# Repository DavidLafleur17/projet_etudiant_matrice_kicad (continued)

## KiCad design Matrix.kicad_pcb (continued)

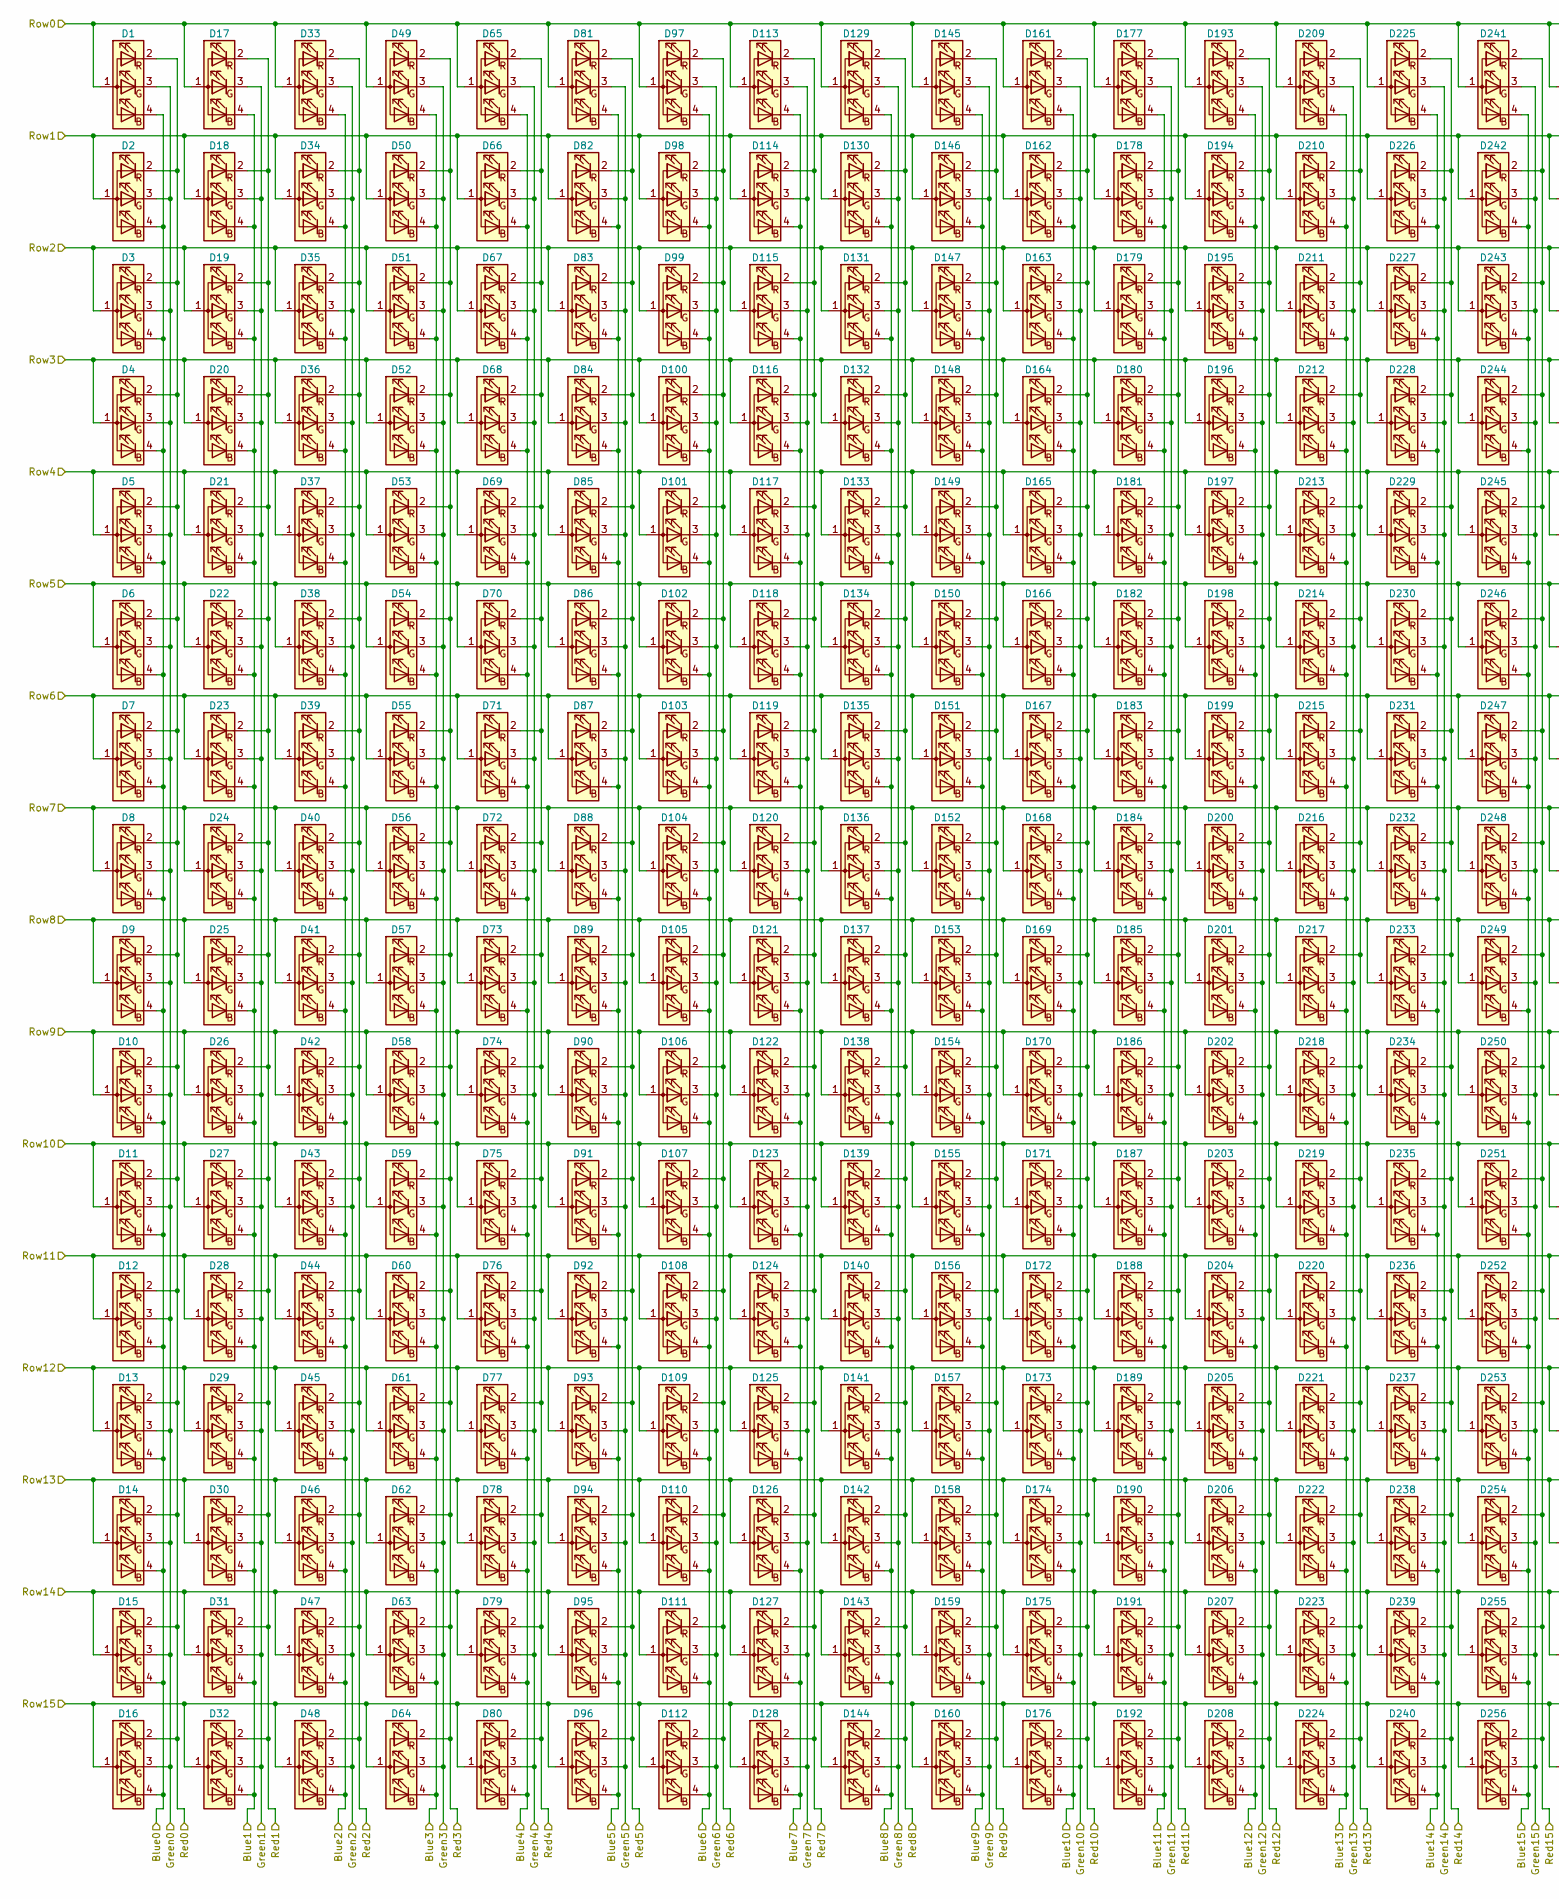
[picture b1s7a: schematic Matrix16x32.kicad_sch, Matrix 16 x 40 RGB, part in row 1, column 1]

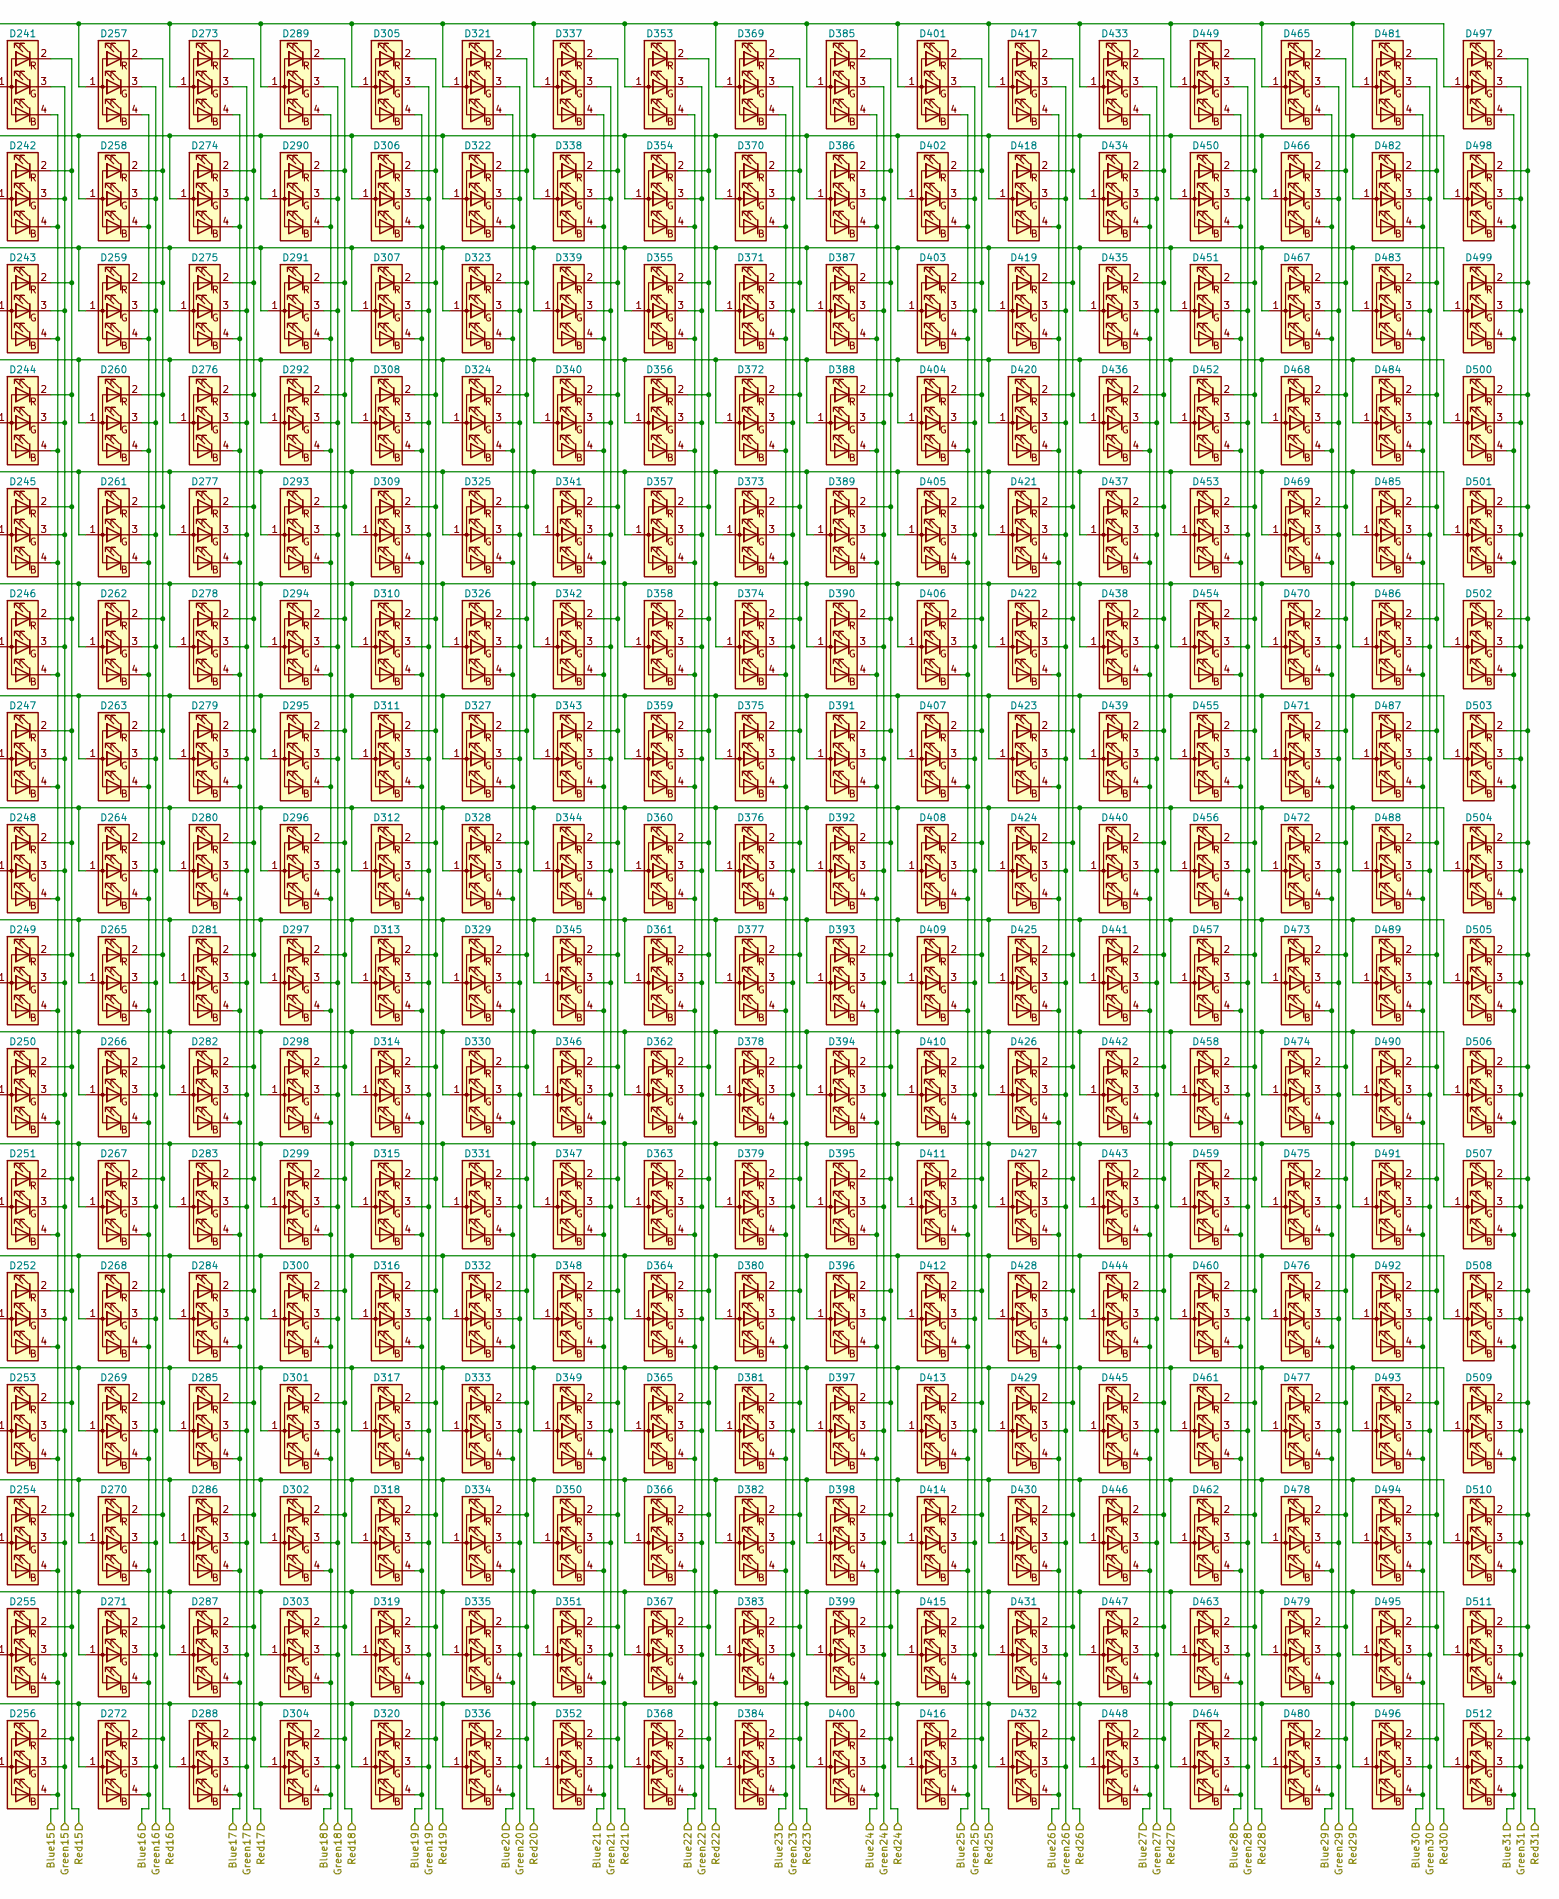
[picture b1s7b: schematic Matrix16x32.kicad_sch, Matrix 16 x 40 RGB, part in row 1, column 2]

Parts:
D1, D2, D3, D4, D5, D6, D7, D8, D9, D10, D11, D12, D13, D14, D15, D16, D17, D18, D19, D20, D21, D22, D23, D24, D25, D26, D27, D28, D29, D30, D31, D32, D33, D34, D35, D36, D37, D38, D39, D40, D41, D42, D43, D44, D45, D46, D47, D48, D49, D50, D51, D52, D53, D54, D55, D56, D57, D58, D59, D60, D61, D62, D63, D64, D65, D66, D67, D68, D69, D70, D71, D72, D73, D74, D75, D76, D77, D78, D79, D80, D81, D82, D83, D84, D85, D86, D87, D88, D89, D90, D91, D92, D93, D94, D95, D96, D97, D98, D99, D100, D101, D102, D103, D104, D105, D106, D107, D108, D109, D110, D111, D112, D113, D114, D115, D116, D117, D118, D119, D120, D121, D122, D123, D124, D125, D126, D127, D128, D129, D130, D131, D132, D133, D134, D135, D136, D137, D138, D139, D140, D141, D142, D143, D144, D145, D146, D147, D148, D149, D150, D151, D152, D153, D154, D155, D156, D157, D158, D159, D160, D161, D162, D163, D164, D165, D166, D167, D168, D169, D170, D171, D172, D173, D174, D175, D176, D177, D178, D179, D180, D181, D182, D183, D184, D185, D186, D187, D188, D189, D190, D191, D192, D193, D194, D195, D196, D197, D198, D199, D200, D201, D202, D203, D204, D205, D206, D207, D208, D209, D210, D211, D212, D213, D214, D215, D216, D217, D218, D219, D220, D221, D222, D223, D224, D225, D226, D227, D228, D229, D230, D231, D232, D233, D234, D235, D236, D237, D238, D239, D240, D241, D242, D243, D244, D245, D246, D247, D248, D249, D250, D251, D252, D253, D254, D255, D256, D257, D258, D259, D260, D261, D262, D263, D264, D265, D266, D267, D268, D269, D270, D271, D272, D273, D274, D275, D276, D277, D278, D279, D280, D281, D282, D283, D284, D285, D286, D287, D288, D289, D290, D291, D292, D293, D294, D295, D296, D297, D298, D299, D300, D301, D302, D303, D304, D305, D306, D307, D308, D309, D310, D311, D312, D313, D314, D315, D316, D317, D318, D319, D320, D321, D322, D323, D324, D325, D326, D327, D328, D329, D330, D331, D332, D333, D334, D335, D336, D337, D338, D339, D340, D341, D342, D343, D344, D345, D346, D347, D348, D349, D350, D351, D352, D353, D354, D355, D356, D357, D358, D359, D360, D361, D362, D363, D364, D365, D366, D367, D368, D369, D370, D371, D372, D373, D374, D375, D376, D377, D378, D379, D380, D381, D382, D383, D384, D385, D386, D387, D388, D389, D390, D391, D392, D393, D394, D395, D396, D397, D398, D399, D400, D401, D402, D403, D404, D405, D406, D407, D408, D409, D410, D411, D412, D413, D414, D415, D416, D417, D418, D419, D420, D421, D422, D423, D424, D425, D426, D427, D428, D429, D430, D431, D432, D433, D434, D435, D436, D437, D438, D439, D440, D441, D442, D443, D444, D445, D446, D447, D448, D449, D450, D451, D452, D453, D454, D455, D456, D457, D458, D459, D460, D461, D462, D463, D464, D465, D466, D467, D468, D469, D470, D471, D472, D473, D474, D475, D476, D477, D478, D479, D480, D481, D482, D483, D484, D485, D486, D487, D488, D489, D490, D491, D492, D493, D494, D495, D496, D497, D498, D499, D500, D501, D502, D503, D504, D505, D506, D507, D508, D509, D510, D511, D512: LED_ARGB; T2133BGR; DigiKey PN 3147-T2133BGR-20C0001U2U1930CT-ND

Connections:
/Blue0: D1.4 (BK), D2.4 (BK), D3.4 (BK), D4.4 (BK), D5.4 (BK), D6.4 (BK), D7.4 (BK), D8.4 (BK), D9.4 (BK), D10.4 (BK), D11.4 (BK), D12.4 (BK), D13.4 (BK), D14.4 (BK), D15.4 (BK), D16.4 (BK); also elsewhere on the board
/Blue1: D17.4 (BK), D18.4 (BK), D19.4 (BK), D20.4 (BK), D21.4 (BK), D22.4 (BK), D23.4 (BK), D24.4 (BK), D25.4 (BK), D26.4 (BK), D27.4 (BK), D28.4 (BK), D29.4 (BK), D30.4 (BK), D31.4 (BK), D32.4 (BK); also elsewhere on the board
/Blue2: D33.4 (BK), D34.4 (BK), D35.4 (BK), D36.4 (BK), D37.4 (BK), D38.4 (BK), D39.4 (BK), D40.4 (BK), D41.4 (BK), D42.4 (BK), D43.4 (BK), D44.4 (BK), D45.4 (BK), D46.4 (BK), D47.4 (BK), D48.4 (BK); also elsewhere on the board
/Blue3: D49.4 (BK), D50.4 (BK), D51.4 (BK), D52.4 (BK), D53.4 (BK), D54.4 (BK), D55.4 (BK), D56.4 (BK), D57.4 (BK), D58.4 (BK), D59.4 (BK), D60.4 (BK), D61.4 (BK), D62.4 (BK), D63.4 (BK), D64.4 (BK); also elsewhere on the board
/Blue4: D65.4 (BK), D66.4 (BK), D67.4 (BK), D68.4 (BK), D69.4 (BK), D70.4 (BK), D71.4 (BK), D72.4 (BK), D73.4 (BK), D74.4 (BK), D75.4 (BK), D76.4 (BK), D77.4 (BK), D78.4 (BK), D79.4 (BK), D80.4 (BK); also elsewhere on the board
/Blue5: D81.4 (BK), D82.4 (BK), D83.4 (BK), D84.4 (BK), D85.4 (BK), D86.4 (BK), D87.4 (BK), D88.4 (BK), D89.4 (BK), D90.4 (BK), D91.4 (BK), D92.4 (BK), D93.4 (BK), D94.4 (BK), D95.4 (BK), D96.4 (BK); also elsewhere on the board
/Blue6: D97.4 (BK), D98.4 (BK), D99.4 (BK), D100.4 (BK), D101.4 (BK), D102.4 (BK), D103.4 (BK), D104.4 (BK), D105.4 (BK), D106.4 (BK), D107.4 (BK), D108.4 (BK), D109.4 (BK), D110.4 (BK), D111.4 (BK), D112.4 (BK); also elsewhere on the board
/Blue7: D113.4 (BK), D114.4 (BK), D115.4 (BK), D116.4 (BK), D117.4 (BK), D118.4 (BK), D119.4 (BK), D120.4 (BK), D121.4 (BK), D122.4 (BK), D123.4 (BK), D124.4 (BK), D125.4 (BK), D126.4 (BK), D127.4 (BK), D128.4 (BK); also elsewhere on the board
/Blue8: D129.4 (BK), D130.4 (BK), D131.4 (BK), D132.4 (BK), D133.4 (BK), D134.4 (BK), D135.4 (BK), D136.4 (BK), D137.4 (BK), D138.4 (BK), D139.4 (BK), D140.4 (BK), D141.4 (BK), D142.4 (BK), D143.4 (BK), D144.4 (BK); also elsewhere on the board
/Blue9: D145.4 (BK), D146.4 (BK), D147.4 (BK), D148.4 (BK), D149.4 (BK), D150.4 (BK), D151.4 (BK), D152.4 (BK), D153.4 (BK), D154.4 (BK), D155.4 (BK), D156.4 (BK), D157.4 (BK), D158.4 (BK), D159.4 (BK), D160.4 (BK); also elsewhere on the board
/Blue10: D161.4 (BK), D162.4 (BK), D163.4 (BK), D164.4 (BK), D165.4 (BK), D166.4 (BK), D167.4 (BK), D168.4 (BK), D169.4 (BK), D170.4 (BK), D171.4 (BK), D172.4 (BK), D173.4 (BK), D174.4 (BK), D175.4 (BK), D176.4 (BK); also elsewhere on the board
/Blue11: D177.4 (BK), D178.4 (BK), D179.4 (BK), D180.4 (BK), D181.4 (BK), D182.4 (BK), D183.4 (BK), D184.4 (BK), D185.4 (BK), D186.4 (BK), D187.4 (BK), D188.4 (BK), D189.4 (BK), D190.4 (BK), D191.4 (BK), D192.4 (BK); also elsewhere on the board
/Blue12: D193.4 (BK), D194.4 (BK), D195.4 (BK), D196.4 (BK), D197.4 (BK), D198.4 (BK), D199.4 (BK), D200.4 (BK), D201.4 (BK), D202.4 (BK), D203.4 (BK), D204.4 (BK), D205.4 (BK), D206.4 (BK), D207.4 (BK), D208.4 (BK); also elsewhere on the board
/Blue13: D209.4 (BK), D210.4 (BK), D211.4 (BK), D212.4 (BK), D213.4 (BK), D214.4 (BK), D215.4 (BK), D216.4 (BK), D217.4 (BK), D218.4 (BK), D219.4 (BK), D220.4 (BK), D221.4 (BK), D222.4 (BK), D223.4 (BK), D224.4 (BK); also elsewhere on the board
/Blue14: D225.4 (BK), D226.4 (BK), D227.4 (BK), D228.4 (BK), D229.4 (BK), D230.4 (BK), D231.4 (BK), D232.4 (BK), D233.4 (BK), D234.4 (BK), D235.4 (BK), D236.4 (BK), D237.4 (BK), D238.4 (BK), D239.4 (BK), D240.4 (BK); also elsewhere on the board
/Blue15: D241.4 (BK), D242.4 (BK), D243.4 (BK), D244.4 (BK), D245.4 (BK), D246.4 (BK), D247.4 (BK), D248.4 (BK), D249.4 (BK), D250.4 (BK), D251.4 (BK), D252.4 (BK), D253.4 (BK), D254.4 (BK), D255.4 (BK), D256.4 (BK); also elsewhere on the board
/Blue16: D257.4 (BK), D258.4 (BK), D259.4 (BK), D260.4 (BK), D261.4 (BK), D262.4 (BK), D263.4 (BK), D264.4 (BK), D265.4 (BK), D266.4 (BK), D267.4 (BK), D268.4 (BK), D269.4 (BK), D270.4 (BK), D271.4 (BK), D272.4 (BK); also elsewhere on the board
/Blue17: D273.4 (BK), D274.4 (BK), D275.4 (BK), D276.4 (BK), D277.4 (BK), D278.4 (BK), D279.4 (BK), D280.4 (BK), D281.4 (BK), D282.4 (BK), D283.4 (BK), D284.4 (BK), D285.4 (BK), D286.4 (BK), D287.4 (BK), D288.4 (BK); also elsewhere on the board
/Blue18: D289.4 (BK), D290.4 (BK), D291.4 (BK), D292.4 (BK), D293.4 (BK), D294.4 (BK), D295.4 (BK), D296.4 (BK), D297.4 (BK), D298.4 (BK), D299.4 (BK), D300.4 (BK), D301.4 (BK), D302.4 (BK), D303.4 (BK), D304.4 (BK); also elsewhere on the board
/Blue19: D305.4 (BK), D306.4 (BK), D307.4 (BK), D308.4 (BK), D309.4 (BK), D310.4 (BK), D311.4 (BK), D312.4 (BK), D313.4 (BK), D314.4 (BK), D315.4 (BK), D316.4 (BK), D317.4 (BK), D318.4 (BK), D319.4 (BK), D320.4 (BK); also elsewhere on the board
/Blue20: D321.4 (BK), D322.4 (BK), D323.4 (BK), D324.4 (BK), D325.4 (BK), D326.4 (BK), D327.4 (BK), D328.4 (BK), D329.4 (BK), D330.4 (BK), D331.4 (BK), D332.4 (BK), D333.4 (BK), D334.4 (BK), D335.4 (BK), D336.4 (BK); also elsewhere on the board
/Blue21: D337.4 (BK), D338.4 (BK), D339.4 (BK), D340.4 (BK), D341.4 (BK), D342.4 (BK), D343.4 (BK), D344.4 (BK), D345.4 (BK), D346.4 (BK), D347.4 (BK), D348.4 (BK), D349.4 (BK), D350.4 (BK), D351.4 (BK), D352.4 (BK); also elsewhere on the board
/Blue22: D353.4 (BK), D354.4 (BK), D355.4 (BK), D356.4 (BK), D357.4 (BK), D358.4 (BK), D359.4 (BK), D360.4 (BK), D361.4 (BK), D362.4 (BK), D363.4 (BK), D364.4 (BK), D365.4 (BK), D366.4 (BK), D367.4 (BK), D368.4 (BK); also elsewhere on the board
/Blue23: D369.4 (BK), D370.4 (BK), D371.4 (BK), D372.4 (BK), D373.4 (BK), D374.4 (BK), D375.4 (BK), D376.4 (BK), D377.4 (BK), D378.4 (BK), D379.4 (BK), D380.4 (BK), D381.4 (BK), D382.4 (BK), D383.4 (BK), D384.4 (BK); also elsewhere on the board
/Blue24: D385.4 (BK), D386.4 (BK), D387.4 (BK), D388.4 (BK), D389.4 (BK), D390.4 (BK), D391.4 (BK), D392.4 (BK), D393.4 (BK), D394.4 (BK), D395.4 (BK), D396.4 (BK), D397.4 (BK), D398.4 (BK), D399.4 (BK), D400.4 (BK); also elsewhere on the board
/Blue25: D401.4 (BK), D402.4 (BK), D403.4 (BK), D404.4 (BK), D405.4 (BK), D406.4 (BK), D407.4 (BK), D408.4 (BK), D409.4 (BK), D410.4 (BK), D411.4 (BK), D412.4 (BK), D413.4 (BK), D414.4 (BK), D415.4 (BK), D416.4 (BK); also elsewhere on the board
/Blue26: D417.4 (BK), D418.4 (BK), D419.4 (BK), D420.4 (BK), D421.4 (BK), D422.4 (BK), D423.4 (BK), D424.4 (BK), D425.4 (BK), D426.4 (BK), D427.4 (BK), D428.4 (BK), D429.4 (BK), D430.4 (BK), D431.4 (BK), D432.4 (BK); also elsewhere on the board
/Blue27: D433.4 (BK), D434.4 (BK), D435.4 (BK), D436.4 (BK), D437.4 (BK), D438.4 (BK), D439.4 (BK), D440.4 (BK), D441.4 (BK), D442.4 (BK), D443.4 (BK), D444.4 (BK), D445.4 (BK), D446.4 (BK), D447.4 (BK), D448.4 (BK); also elsewhere on the board
/Blue28: D449.4 (BK), D450.4 (BK), D451.4 (BK), D452.4 (BK), D453.4 (BK), D454.4 (BK), D455.4 (BK), D456.4 (BK), D457.4 (BK), D458.4 (BK), D459.4 (BK), D460.4 (BK), D461.4 (BK), D462.4 (BK), D463.4 (BK), D464.4 (BK); also elsewhere on the board
/Blue29: D465.4 (BK), D466.4 (BK), D467.4 (BK), D468.4 (BK), D469.4 (BK), D470.4 (BK), D471.4 (BK), D472.4 (BK), D473.4 (BK), D474.4 (BK), D475.4 (BK), D476.4 (BK), D477.4 (BK), D478.4 (BK), D479.4 (BK), D480.4 (BK); also elsewhere on the board
/Blue30: D481.4 (BK), D482.4 (BK), D483.4 (BK), D484.4 (BK), D485.4 (BK), D486.4 (BK), D487.4 (BK), D488.4 (BK), D489.4 (BK), D490.4 (BK), D491.4 (BK), D492.4 (BK), D493.4 (BK), D494.4 (BK), D495.4 (BK), D496.4 (BK); also elsewhere on the board
/Blue31: D497.4 (BK), D498.4 (BK), D499.4 (BK), D500.4 (BK), D501.4 (BK), D502.4 (BK), D503.4 (BK), D504.4 (BK), D505.4 (BK), D506.4 (BK), D507.4 (BK), D508.4 (BK), D509.4 (BK), D510.4 (BK), D511.4 (BK), D512.4 (BK); also elsewhere on the board
/Decoder/Row0: D1.1 (A), D17.1 (A), D33.1 (A), D49.1 (A), D65.1 (A), D81.1 (A), D97.1 (A), D113.1 (A), D129.1 (A), D145.1 (A), D161.1 (A), D177.1 (A), D193.1 (A), D209.1 (A), D225.1 (A), D241.1 (A), D257.1 (A), D273.1 (A), D289.1 (A), D305.1 (A), D321.1 (A), D337.1 (A), D353.1 (A), D369.1 (A), D385.1 (A), D401.1 (A), D417.1 (A), D433.1 (A), D449.1 (A), D465.1 (A), D481.1 (A), D497.1 (A); also elsewhere on the board
/Decoder/Row1: D2.1 (A), D18.1 (A), D34.1 (A), D50.1 (A), D66.1 (A), D82.1 (A), D98.1 (A), D114.1 (A), D130.1 (A), D146.1 (A), D162.1 (A), D178.1 (A), D194.1 (A), D210.1 (A), D226.1 (A), D242.1 (A), D258.1 (A), D274.1 (A), D290.1 (A), D306.1 (A), D322.1 (A), D338.1 (A), D354.1 (A), D370.1 (A), D386.1 (A), D402.1 (A), D418.1 (A), D434.1 (A), D450.1 (A), D466.1 (A), D482.1 (A), D498.1 (A); also elsewhere on the board
/Decoder/Row2: D3.1 (A), D19.1 (A), D35.1 (A), D51.1 (A), D67.1 (A), D83.1 (A), D99.1 (A), D115.1 (A), D131.1 (A), D147.1 (A), D163.1 (A), D179.1 (A), D195.1 (A), D211.1 (A), D227.1 (A), D243.1 (A), D259.1 (A), D275.1 (A), D291.1 (A), D307.1 (A), D323.1 (A), D339.1 (A), D355.1 (A), D371.1 (A), D387.1 (A), D403.1 (A), D419.1 (A), D435.1 (A), D451.1 (A), D467.1 (A), D483.1 (A), D499.1 (A); also elsewhere on the board
/Decoder/Row3: D4.1 (A), D20.1 (A), D36.1 (A), D52.1 (A), D68.1 (A), D84.1 (A), D100.1 (A), D116.1 (A), D132.1 (A), D148.1 (A), D164.1 (A), D180.1 (A), D196.1 (A), D212.1 (A), D228.1 (A), D244.1 (A), D260.1 (A), D276.1 (A), D292.1 (A), D308.1 (A), D324.1 (A), D340.1 (A), D356.1 (A), D372.1 (A), D388.1 (A), D404.1 (A), D420.1 (A), D436.1 (A), D452.1 (A), D468.1 (A), D484.1 (A), D500.1 (A); also elsewhere on the board
/Decoder/Row4: D5.1 (A), D21.1 (A), D37.1 (A), D53.1 (A), D69.1 (A), D85.1 (A), D101.1 (A), D117.1 (A), D133.1 (A), D149.1 (A), D165.1 (A), D181.1 (A), D197.1 (A), D213.1 (A), D229.1 (A), D245.1 (A), D261.1 (A), D277.1 (A), D293.1 (A), D309.1 (A), D325.1 (A), D341.1 (A), D357.1 (A), D373.1 (A), D389.1 (A), D405.1 (A), D421.1 (A), D437.1 (A), D453.1 (A), D469.1 (A), D485.1 (A), D501.1 (A); also elsewhere on the board
/Decoder/Row5: D6.1 (A), D22.1 (A), D38.1 (A), D54.1 (A), D70.1 (A), D86.1 (A), D102.1 (A), D118.1 (A), D134.1 (A), D150.1 (A), D166.1 (A), D182.1 (A), D198.1 (A), D214.1 (A), D230.1 (A), D246.1 (A), D262.1 (A), D278.1 (A), D294.1 (A), D310.1 (A), D326.1 (A), D342.1 (A), D358.1 (A), D374.1 (A), D390.1 (A), D406.1 (A), D422.1 (A), D438.1 (A), D454.1 (A), D470.1 (A), D486.1 (A), D502.1 (A); also elsewhere on the board
/Decoder/Row6: D7.1 (A), D23.1 (A), D39.1 (A), D55.1 (A), D71.1 (A), D87.1 (A), D103.1 (A), D119.1 (A), D135.1 (A), D151.1 (A), D167.1 (A), D183.1 (A), D199.1 (A), D215.1 (A), D231.1 (A), D247.1 (A), D263.1 (A), D279.1 (A), D295.1 (A), D311.1 (A), D327.1 (A), D343.1 (A), D359.1 (A), D375.1 (A), D391.1 (A), D407.1 (A), D423.1 (A), D439.1 (A), D455.1 (A), D471.1 (A), D487.1 (A), D503.1 (A); also elsewhere on the board
/Decoder/Row7: D8.1 (A), D24.1 (A), D40.1 (A), D56.1 (A), D72.1 (A), D88.1 (A), D104.1 (A), D120.1 (A), D136.1 (A), D152.1 (A), D168.1 (A), D184.1 (A), D200.1 (A), D216.1 (A), D232.1 (A), D248.1 (A), D264.1 (A), D280.1 (A), D296.1 (A), D312.1 (A), D328.1 (A), D344.1 (A), D360.1 (A), D376.1 (A), D392.1 (A), D408.1 (A), D424.1 (A), D440.1 (A), D456.1 (A), D472.1 (A), D488.1 (A), D504.1 (A); also elsewhere on the board
/Decoder/Row8: D9.1 (A), D25.1 (A), D41.1 (A), D57.1 (A), D73.1 (A), D89.1 (A), D105.1 (A), D121.1 (A), D137.1 (A), D153.1 (A), D169.1 (A), D185.1 (A), D201.1 (A), D217.1 (A), D233.1 (A), D249.1 (A), D265.1 (A), D281.1 (A), D297.1 (A), D313.1 (A), D329.1 (A), D345.1 (A), D361.1 (A), D377.1 (A), D393.1 (A), D409.1 (A), D425.1 (A), D441.1 (A), D457.1 (A), D473.1 (A), D489.1 (A), D505.1 (A); also elsewhere on the board
/Decoder/Row9: D10.1 (A), D26.1 (A), D42.1 (A), D58.1 (A), D74.1 (A), D90.1 (A), D106.1 (A), D122.1 (A), D138.1 (A), D154.1 (A), D170.1 (A), D186.1 (A), D202.1 (A), D218.1 (A), D234.1 (A), D250.1 (A), D266.1 (A), D282.1 (A), D298.1 (A), D314.1 (A), D330.1 (A), D346.1 (A), D362.1 (A), D378.1 (A), D394.1 (A), D410.1 (A), D426.1 (A), D442.1 (A), D458.1 (A), D474.1 (A), D490.1 (A), D506.1 (A); also elsewhere on the board
/Decoder/Row10: D11.1 (A), D27.1 (A), D43.1 (A), D59.1 (A), D75.1 (A), D91.1 (A), D107.1 (A), D123.1 (A), D139.1 (A), D155.1 (A), D171.1 (A), D187.1 (A), D203.1 (A), D219.1 (A), D235.1 (A), D251.1 (A), D267.1 (A), D283.1 (A), D299.1 (A), D315.1 (A), D331.1 (A), D347.1 (A), D363.1 (A), D379.1 (A), D395.1 (A), D411.1 (A), D427.1 (A), D443.1 (A), D459.1 (A), D475.1 (A), D491.1 (A), D507.1 (A); also elsewhere on the board
/Decoder/Row11: D12.1 (A), D28.1 (A), D44.1 (A), D60.1 (A), D76.1 (A), D92.1 (A), D108.1 (A), D124.1 (A), D140.1 (A), D156.1 (A), D172.1 (A), D188.1 (A), D204.1 (A), D220.1 (A), D236.1 (A), D252.1 (A), D268.1 (A), D284.1 (A), D300.1 (A), D316.1 (A), D332.1 (A), D348.1 (A), D364.1 (A), D380.1 (A), D396.1 (A), D412.1 (A), D428.1 (A), D444.1 (A), D460.1 (A), D476.1 (A), D492.1 (A), D508.1 (A); also elsewhere on the board
/Decoder/Row12: D13.1 (A), D29.1 (A), D45.1 (A), D61.1 (A), D77.1 (A), D93.1 (A), D109.1 (A), D125.1 (A), D141.1 (A), D157.1 (A), D173.1 (A), D189.1 (A), D205.1 (A), D221.1 (A), D237.1 (A), D253.1 (A), D269.1 (A), D285.1 (A), D301.1 (A), D317.1 (A), D333.1 (A), D349.1 (A), D365.1 (A), D381.1 (A), D397.1 (A), D413.1 (A), D429.1 (A), D445.1 (A), D461.1 (A), D477.1 (A), D493.1 (A), D509.1 (A); also elsewhere on the board
/Decoder/Row13: D14.1 (A), D30.1 (A), D46.1 (A), D62.1 (A), D78.1 (A), D94.1 (A), D110.1 (A), D126.1 (A), D142.1 (A), D158.1 (A), D174.1 (A), D190.1 (A), D206.1 (A), D222.1 (A), D238.1 (A), D254.1 (A), D270.1 (A), D286.1 (A), D302.1 (A), D318.1 (A), D334.1 (A), D350.1 (A), D366.1 (A), D382.1 (A), D398.1 (A), D414.1 (A), D430.1 (A), D446.1 (A), D462.1 (A), D478.1 (A), D494.1 (A), D510.1 (A); also elsewhere on the board
/Decoder/Row14: D15.1 (A), D31.1 (A), D47.1 (A), D63.1 (A), D79.1 (A), D95.1 (A), D111.1 (A), D127.1 (A), D143.1 (A), D159.1 (A), D175.1 (A), D191.1 (A), D207.1 (A), D223.1 (A), D239.1 (A), D255.1 (A), D271.1 (A), D287.1 (A), D303.1 (A), D319.1 (A), D335.1 (A), D351.1 (A), D367.1 (A), D383.1 (A), D399.1 (A), D415.1 (A), D431.1 (A), D447.1 (A), D463.1 (A), D479.1 (A), D495.1 (A), D511.1 (A); also elsewhere on the board
/Decoder/Row15: D16.1 (A), D32.1 (A), D48.1 (A), D64.1 (A), D80.1 (A), D96.1 (A), D112.1 (A), D128.1 (A), D144.1 (A), D160.1 (A), D176.1 (A), D192.1 (A), D208.1 (A), D224.1 (A), D240.1 (A), D256.1 (A), D272.1 (A), D288.1 (A), D304.1 (A), D320.1 (A), D336.1 (A), D352.1 (A), D368.1 (A), D384.1 (A), D400.1 (A), D416.1 (A), D432.1 (A), D448.1 (A), D464.1 (A), D480.1 (A), D496.1 (A), D512.1 (A); also elsewhere on the board
/Green0: D1.3 (GK), D2.3 (GK), D3.3 (GK), D4.3 (GK), D5.3 (GK), D6.3 (GK), D7.3 (GK), D8.3 (GK), D9.3 (GK), D10.3 (GK), D11.3 (GK), D12.3 (GK), D13.3 (GK), D14.3 (GK), D15.3 (GK), D16.3 (GK); also elsewhere on the board
/Green1: D17.3 (GK), D18.3 (GK), D19.3 (GK), D20.3 (GK), D21.3 (GK), D22.3 (GK), D23.3 (GK), D24.3 (GK), D25.3 (GK), D26.3 (GK), D27.3 (GK), D28.3 (GK), D29.3 (GK), D30.3 (GK), D31.3 (GK), D32.3 (GK); also elsewhere on the board
/Green2: D33.3 (GK), D34.3 (GK), D35.3 (GK), D36.3 (GK), D37.3 (GK), D38.3 (GK), D39.3 (GK), D40.3 (GK), D41.3 (GK), D42.3 (GK), D43.3 (GK), D44.3 (GK), D45.3 (GK), D46.3 (GK), D47.3 (GK), D48.3 (GK); also elsewhere on the board
/Green3: D49.3 (GK), D50.3 (GK), D51.3 (GK), D52.3 (GK), D53.3 (GK), D54.3 (GK), D55.3 (GK), D56.3 (GK), D57.3 (GK), D58.3 (GK), D59.3 (GK), D60.3 (GK), D61.3 (GK), D62.3 (GK), D63.3 (GK), D64.3 (GK); also elsewhere on the board
/Green4: D65.3 (GK), D66.3 (GK), D67.3 (GK), D68.3 (GK), D69.3 (GK), D70.3 (GK), D71.3 (GK), D72.3 (GK), D73.3 (GK), D74.3 (GK), D75.3 (GK), D76.3 (GK), D77.3 (GK), D78.3 (GK), D79.3 (GK), D80.3 (GK); also elsewhere on the board
/Green5: D81.3 (GK), D82.3 (GK), D83.3 (GK), D84.3 (GK), D85.3 (GK), D86.3 (GK), D87.3 (GK), D88.3 (GK), D89.3 (GK), D90.3 (GK), D91.3 (GK), D92.3 (GK), D93.3 (GK), D94.3 (GK), D95.3 (GK), D96.3 (GK); also elsewhere on the board
/Green6: D97.3 (GK), D98.3 (GK), D99.3 (GK), D100.3 (GK), D101.3 (GK), D102.3 (GK), D103.3 (GK), D104.3 (GK), D105.3 (GK), D106.3 (GK), D107.3 (GK), D108.3 (GK), D109.3 (GK), D110.3 (GK), D111.3 (GK), D112.3 (GK); also elsewhere on the board
/Green7: D113.3 (GK), D114.3 (GK), D115.3 (GK), D116.3 (GK), D117.3 (GK), D118.3 (GK), D119.3 (GK), D120.3 (GK), D121.3 (GK), D122.3 (GK), D123.3 (GK), D124.3 (GK), D125.3 (GK), D126.3 (GK), D127.3 (GK), D128.3 (GK); also elsewhere on the board
/Green8: D129.3 (GK), D130.3 (GK), D131.3 (GK), D132.3 (GK), D133.3 (GK), D134.3 (GK), D135.3 (GK), D136.3 (GK), D137.3 (GK), D138.3 (GK), D139.3 (GK), D140.3 (GK), D141.3 (GK), D142.3 (GK), D143.3 (GK), D144.3 (GK); also elsewhere on the board
/Green9: D145.3 (GK), D146.3 (GK), D147.3 (GK), D148.3 (GK), D149.3 (GK), D150.3 (GK), D151.3 (GK), D152.3 (GK), D153.3 (GK), D154.3 (GK), D155.3 (GK), D156.3 (GK), D157.3 (GK), D158.3 (GK), D159.3 (GK), D160.3 (GK); also elsewhere on the board
/Green10: D161.3 (GK), D162.3 (GK), D163.3 (GK), D164.3 (GK), D165.3 (GK), D166.3 (GK), D167.3 (GK), D168.3 (GK), D169.3 (GK), D170.3 (GK), D171.3 (GK), D172.3 (GK), D173.3 (GK), D174.3 (GK), D175.3 (GK), D176.3 (GK); also elsewhere on the board
/Green11: D177.3 (GK), D178.3 (GK), D179.3 (GK), D180.3 (GK), D181.3 (GK), D182.3 (GK), D183.3 (GK), D184.3 (GK), D185.3 (GK), D186.3 (GK), D187.3 (GK), D188.3 (GK), D189.3 (GK), D190.3 (GK), D191.3 (GK), D192.3 (GK); also elsewhere on the board
/Green12: D193.3 (GK), D194.3 (GK), D195.3 (GK), D196.3 (GK), D197.3 (GK), D198.3 (GK), D199.3 (GK), D200.3 (GK), D201.3 (GK), D202.3 (GK), D203.3 (GK), D204.3 (GK), D205.3 (GK), D206.3 (GK), D207.3 (GK), D208.3 (GK); also elsewhere on the board
/Green13: D209.3 (GK), D210.3 (GK), D211.3 (GK), D212.3 (GK), D213.3 (GK), D214.3 (GK), D215.3 (GK), D216.3 (GK), D217.3 (GK), D218.3 (GK), D219.3 (GK), D220.3 (GK), D221.3 (GK), D222.3 (GK), D223.3 (GK), D224.3 (GK); also elsewhere on the board
/Green14: D225.3 (GK), D226.3 (GK), D227.3 (GK), D228.3 (GK), D229.3 (GK), D230.3 (GK), D231.3 (GK), D232.3 (GK), D233.3 (GK), D234.3 (GK), D235.3 (GK), D236.3 (GK), D237.3 (GK), D238.3 (GK), D239.3 (GK), D240.3 (GK); also elsewhere on the board
/Green15: D241.3 (GK), D242.3 (GK), D243.3 (GK), D244.3 (GK), D245.3 (GK), D246.3 (GK), D247.3 (GK), D248.3 (GK), D249.3 (GK), D250.3 (GK), D251.3 (GK), D252.3 (GK), D253.3 (GK), D254.3 (GK), D255.3 (GK), D256.3 (GK); also elsewhere on the board
/Green16: D257.3 (GK), D258.3 (GK), D259.3 (GK), D260.3 (GK), D261.3 (GK), D262.3 (GK), D263.3 (GK), D264.3 (GK), D265.3 (GK), D266.3 (GK), D267.3 (GK), D268.3 (GK), D269.3 (GK), D270.3 (GK), D271.3 (GK), D272.3 (GK); also elsewhere on the board
/Green17: D273.3 (GK), D274.3 (GK), D275.3 (GK), D276.3 (GK), D277.3 (GK), D278.3 (GK), D279.3 (GK), D280.3 (GK), D281.3 (GK), D282.3 (GK), D283.3 (GK), D284.3 (GK), D285.3 (GK), D286.3 (GK), D287.3 (GK), D288.3 (GK); also elsewhere on the board
/Green18: D289.3 (GK), D290.3 (GK), D291.3 (GK), D292.3 (GK), D293.3 (GK), D294.3 (GK), D295.3 (GK), D296.3 (GK), D297.3 (GK), D298.3 (GK), D299.3 (GK), D300.3 (GK), D301.3 (GK), D302.3 (GK), D303.3 (GK), D304.3 (GK); also elsewhere on the board
/Green19: D305.3 (GK), D306.3 (GK), D307.3 (GK), D308.3 (GK), D309.3 (GK), D310.3 (GK), D311.3 (GK), D312.3 (GK), D313.3 (GK), D314.3 (GK), D315.3 (GK), D316.3 (GK), D317.3 (GK), D318.3 (GK), D319.3 (GK), D320.3 (GK); also elsewhere on the board
/Green20: D321.3 (GK), D322.3 (GK), D323.3 (GK), D324.3 (GK), D325.3 (GK), D326.3 (GK), D327.3 (GK), D328.3 (GK), D329.3 (GK), D330.3 (GK), D331.3 (GK), D332.3 (GK), D333.3 (GK), D334.3 (GK), D335.3 (GK), D336.3 (GK); also elsewhere on the board
/Green21: D337.3 (GK), D338.3 (GK), D339.3 (GK), D340.3 (GK), D341.3 (GK), D342.3 (GK), D343.3 (GK), D344.3 (GK), D345.3 (GK), D346.3 (GK), D347.3 (GK), D348.3 (GK), D349.3 (GK), D350.3 (GK), D351.3 (GK), D352.3 (GK); also elsewhere on the board
/Green22: D353.3 (GK), D354.3 (GK), D355.3 (GK), D356.3 (GK), D357.3 (GK), D358.3 (GK), D359.3 (GK), D360.3 (GK), D361.3 (GK), D362.3 (GK), D363.3 (GK), D364.3 (GK), D365.3 (GK), D366.3 (GK), D367.3 (GK), D368.3 (GK); also elsewhere on the board
/Green23: D369.3 (GK), D370.3 (GK), D371.3 (GK), D372.3 (GK), D373.3 (GK), D374.3 (GK), D375.3 (GK), D376.3 (GK), D377.3 (GK), D378.3 (GK), D379.3 (GK), D380.3 (GK), D381.3 (GK), D382.3 (GK), D383.3 (GK), D384.3 (GK); also elsewhere on the board
/Green24: D385.3 (GK), D386.3 (GK), D387.3 (GK), D388.3 (GK), D389.3 (GK), D390.3 (GK), D391.3 (GK), D392.3 (GK), D393.3 (GK), D394.3 (GK), D395.3 (GK), D396.3 (GK), D397.3 (GK), D398.3 (GK), D399.3 (GK), D400.3 (GK); also elsewhere on the board
/Green25: D401.3 (GK), D402.3 (GK), D403.3 (GK), D404.3 (GK), D405.3 (GK), D406.3 (GK), D407.3 (GK), D408.3 (GK), D409.3 (GK), D410.3 (GK), D411.3 (GK), D412.3 (GK), D413.3 (GK), D414.3 (GK), D415.3 (GK), D416.3 (GK); also elsewhere on the board
/Green26: D417.3 (GK), D418.3 (GK), D419.3 (GK), D420.3 (GK), D421.3 (GK), D422.3 (GK), D423.3 (GK), D424.3 (GK), D425.3 (GK), D426.3 (GK), D427.3 (GK), D428.3 (GK), D429.3 (GK), D430.3 (GK), D431.3 (GK), D432.3 (GK); also elsewhere on the board
/Green27: D433.3 (GK), D434.3 (GK), D435.3 (GK), D436.3 (GK), D437.3 (GK), D438.3 (GK), D439.3 (GK), D440.3 (GK), D441.3 (GK), D442.3 (GK), D443.3 (GK), D444.3 (GK), D445.3 (GK), D446.3 (GK), D447.3 (GK), D448.3 (GK); also elsewhere on the board
/Green28: D449.3 (GK), D450.3 (GK), D451.3 (GK), D452.3 (GK), D453.3 (GK), D454.3 (GK), D455.3 (GK), D456.3 (GK), D457.3 (GK), D458.3 (GK), D459.3 (GK), D460.3 (GK), D461.3 (GK), D462.3 (GK), D463.3 (GK), D464.3 (GK); also elsewhere on the board
/Green29: D465.3 (GK), D466.3 (GK), D467.3 (GK), D468.3 (GK), D469.3 (GK), D470.3 (GK), D471.3 (GK), D472.3 (GK), D473.3 (GK), D474.3 (GK), D475.3 (GK), D476.3 (GK), D477.3 (GK), D478.3 (GK), D479.3 (GK), D480.3 (GK); also elsewhere on the board
/Green30: D481.3 (GK), D482.3 (GK), D483.3 (GK), D484.3 (GK), D485.3 (GK), D486.3 (GK), D487.3 (GK), D488.3 (GK), D489.3 (GK), D490.3 (GK), D491.3 (GK), D492.3 (GK), D493.3 (GK), D494.3 (GK), D495.3 (GK), D496.3 (GK); also elsewhere on the board
/Green31: D497.3 (GK), D498.3 (GK), D499.3 (GK), D500.3 (GK), D501.3 (GK), D502.3 (GK), D503.3 (GK), D504.3 (GK), D505.3 (GK), D506.3 (GK), D507.3 (GK), D508.3 (GK), D509.3 (GK), D510.3 (GK), D511.3 (GK), D512.3 (GK); also elsewhere on the board
/Red0: D1.2 (RK), D2.2 (RK), D3.2 (RK), D4.2 (RK), D5.2 (RK), D6.2 (RK), D7.2 (RK), D8.2 (RK), D9.2 (RK), D10.2 (RK), D11.2 (RK), D12.2 (RK), D13.2 (RK), D14.2 (RK), D15.2 (RK), D16.2 (RK); also elsewhere on the board
/Red1: D17.2 (RK), D18.2 (RK), D19.2 (RK), D20.2 (RK), D21.2 (RK), D22.2 (RK), D23.2 (RK), D24.2 (RK), D25.2 (RK), D26.2 (RK), D27.2 (RK), D28.2 (RK), D29.2 (RK), D30.2 (RK), D31.2 (RK), D32.2 (RK); also elsewhere on the board
/Red2: D33.2 (RK), D34.2 (RK), D35.2 (RK), D36.2 (RK), D37.2 (RK), D38.2 (RK), D39.2 (RK), D40.2 (RK), D41.2 (RK), D42.2 (RK), D43.2 (RK), D44.2 (RK), D45.2 (RK), D46.2 (RK), D47.2 (RK), D48.2 (RK); also elsewhere on the board
/Red3: D49.2 (RK), D50.2 (RK), D51.2 (RK), D52.2 (RK), D53.2 (RK), D54.2 (RK), D55.2 (RK), D56.2 (RK), D57.2 (RK), D58.2 (RK), D59.2 (RK), D60.2 (RK), D61.2 (RK), D62.2 (RK), D63.2 (RK), D64.2 (RK); also elsewhere on the board
/Red4: D65.2 (RK), D66.2 (RK), D67.2 (RK), D68.2 (RK), D69.2 (RK), D70.2 (RK), D71.2 (RK), D72.2 (RK), D73.2 (RK), D74.2 (RK), D75.2 (RK), D76.2 (RK), D77.2 (RK), D78.2 (RK), D79.2 (RK), D80.2 (RK); also elsewhere on the board
/Red5: D81.2 (RK), D82.2 (RK), D83.2 (RK), D84.2 (RK), D85.2 (RK), D86.2 (RK), D87.2 (RK), D88.2 (RK), D89.2 (RK), D90.2 (RK), D91.2 (RK), D92.2 (RK), D93.2 (RK), D94.2 (RK), D95.2 (RK), D96.2 (RK); also elsewhere on the board
/Red6: D97.2 (RK), D98.2 (RK), D99.2 (RK), D100.2 (RK), D101.2 (RK), D102.2 (RK), D103.2 (RK), D104.2 (RK), D105.2 (RK), D106.2 (RK), D107.2 (RK), D108.2 (RK), D109.2 (RK), D110.2 (RK), D111.2 (RK), D112.2 (RK); also elsewhere on the board
/Red7: D113.2 (RK), D114.2 (RK), D115.2 (RK), D116.2 (RK), D117.2 (RK), D118.2 (RK), D119.2 (RK), D120.2 (RK), D121.2 (RK), D122.2 (RK), D123.2 (RK), D124.2 (RK), D125.2 (RK), D126.2 (RK), D127.2 (RK), D128.2 (RK); also elsewhere on the board
/Red8: D129.2 (RK), D130.2 (RK), D131.2 (RK), D132.2 (RK), D133.2 (RK), D134.2 (RK), D135.2 (RK), D136.2 (RK), D137.2 (RK), D138.2 (RK), D139.2 (RK), D140.2 (RK), D141.2 (RK), D142.2 (RK), D143.2 (RK), D144.2 (RK); also elsewhere on the board
/Red9: D145.2 (RK), D146.2 (RK), D147.2 (RK), D148.2 (RK), D149.2 (RK), D150.2 (RK), D151.2 (RK), D152.2 (RK), D153.2 (RK), D154.2 (RK), D155.2 (RK), D156.2 (RK), D157.2 (RK), D158.2 (RK), D159.2 (RK), D160.2 (RK); also elsewhere on the board
/Red10: D161.2 (RK), D162.2 (RK), D163.2 (RK), D164.2 (RK), D165.2 (RK), D166.2 (RK), D167.2 (RK), D168.2 (RK), D169.2 (RK), D170.2 (RK), D171.2 (RK), D172.2 (RK), D173.2 (RK), D174.2 (RK), D175.2 (RK), D176.2 (RK); also elsewhere on the board
/Red11: D177.2 (RK), D178.2 (RK), D179.2 (RK), D180.2 (RK), D181.2 (RK), D182.2 (RK), D183.2 (RK), D184.2 (RK), D185.2 (RK), D186.2 (RK), D187.2 (RK), D188.2 (RK), D189.2 (RK), D190.2 (RK), D191.2 (RK), D192.2 (RK); also elsewhere on the board
/Red12: D193.2 (RK), D194.2 (RK), D195.2 (RK), D196.2 (RK), D197.2 (RK), D198.2 (RK), D199.2 (RK), D200.2 (RK), D201.2 (RK), D202.2 (RK), D203.2 (RK), D204.2 (RK), D205.2 (RK), D206.2 (RK), D207.2 (RK), D208.2 (RK); also elsewhere on the board
/Red13: D209.2 (RK), D210.2 (RK), D211.2 (RK), D212.2 (RK), D213.2 (RK), D214.2 (RK), D215.2 (RK), D216.2 (RK), D217.2 (RK), D218.2 (RK), D219.2 (RK), D220.2 (RK), D221.2 (RK), D222.2 (RK), D223.2 (RK), D224.2 (RK); also elsewhere on the board
/Red14: D225.2 (RK), D226.2 (RK), D227.2 (RK), D228.2 (RK), D229.2 (RK), D230.2 (RK), D231.2 (RK), D232.2 (RK), D233.2 (RK), D234.2 (RK), D235.2 (RK), D236.2 (RK), D237.2 (RK), D238.2 (RK), D239.2 (RK), D240.2 (RK); also elsewhere on the board
/Red15: D241.2 (RK), D242.2 (RK), D243.2 (RK), D244.2 (RK), D245.2 (RK), D246.2 (RK), D247.2 (RK), D248.2 (RK), D249.2 (RK), D250.2 (RK), D251.2 (RK), D252.2 (RK), D253.2 (RK), D254.2 (RK), D255.2 (RK), D256.2 (RK); also elsewhere on the board
/Red16: D257.2 (RK), D258.2 (RK), D259.2 (RK), D260.2 (RK), D261.2 (RK), D262.2 (RK), D263.2 (RK), D264.2 (RK), D265.2 (RK), D266.2 (RK), D267.2 (RK), D268.2 (RK), D269.2 (RK), D270.2 (RK), D271.2 (RK), D272.2 (RK); also elsewhere on the board
/Red17: D273.2 (RK), D274.2 (RK), D275.2 (RK), D276.2 (RK), D277.2 (RK), D278.2 (RK), D279.2 (RK), D280.2 (RK), D281.2 (RK), D282.2 (RK), D283.2 (RK), D284.2 (RK), D285.2 (RK), D286.2 (RK), D287.2 (RK), D288.2 (RK); also elsewhere on the board
/Red18: D289.2 (RK), D290.2 (RK), D291.2 (RK), D292.2 (RK), D293.2 (RK), D294.2 (RK), D295.2 (RK), D296.2 (RK), D297.2 (RK), D298.2 (RK), D299.2 (RK), D300.2 (RK), D301.2 (RK), D302.2 (RK), D303.2 (RK), D304.2 (RK); also elsewhere on the board
/Red19: D305.2 (RK), D306.2 (RK), D307.2 (RK), D308.2 (RK), D309.2 (RK), D310.2 (RK), D311.2 (RK), D312.2 (RK), D313.2 (RK), D314.2 (RK), D315.2 (RK), D316.2 (RK), D317.2 (RK), D318.2 (RK), D319.2 (RK), D320.2 (RK); also elsewhere on the board
/Red20: D321.2 (RK), D322.2 (RK), D323.2 (RK), D324.2 (RK), D325.2 (RK), D326.2 (RK), D327.2 (RK), D328.2 (RK), D329.2 (RK), D330.2 (RK), D331.2 (RK), D332.2 (RK), D333.2 (RK), D334.2 (RK), D335.2 (RK), D336.2 (RK); also elsewhere on the board
/Red21: D337.2 (RK), D338.2 (RK), D339.2 (RK), D340.2 (RK), D341.2 (RK), D342.2 (RK), D343.2 (RK), D344.2 (RK), D345.2 (RK), D346.2 (RK), D347.2 (RK), D348.2 (RK), D349.2 (RK), D350.2 (RK), D351.2 (RK), D352.2 (RK); also elsewhere on the board
/Red22: D353.2 (RK), D354.2 (RK), D355.2 (RK), D356.2 (RK), D357.2 (RK), D358.2 (RK), D359.2 (RK), D360.2 (RK), D361.2 (RK), D362.2 (RK), D363.2 (RK), D364.2 (RK), D365.2 (RK), D366.2 (RK), D367.2 (RK), D368.2 (RK); also elsewhere on the board
/Red23: D369.2 (RK), D370.2 (RK), D371.2 (RK), D372.2 (RK), D373.2 (RK), D374.2 (RK), D375.2 (RK), D376.2 (RK), D377.2 (RK), D378.2 (RK), D379.2 (RK), D380.2 (RK), D381.2 (RK), D382.2 (RK), D383.2 (RK), D384.2 (RK); also elsewhere on the board
/Red24: D385.2 (RK), D386.2 (RK), D387.2 (RK), D388.2 (RK), D389.2 (RK), D390.2 (RK), D391.2 (RK), D392.2 (RK), D393.2 (RK), D394.2 (RK), D395.2 (RK), D396.2 (RK), D397.2 (RK), D398.2 (RK), D399.2 (RK), D400.2 (RK); also elsewhere on the board
/Red25: D401.2 (RK), D402.2 (RK), D403.2 (RK), D404.2 (RK), D405.2 (RK), D406.2 (RK), D407.2 (RK), D408.2 (RK), D409.2 (RK), D410.2 (RK), D411.2 (RK), D412.2 (RK), D413.2 (RK), D414.2 (RK), D415.2 (RK), D416.2 (RK); also elsewhere on the board
/Red26: D417.2 (RK), D418.2 (RK), D419.2 (RK), D420.2 (RK), D421.2 (RK), D422.2 (RK), D423.2 (RK), D424.2 (RK), D425.2 (RK), D426.2 (RK), D427.2 (RK), D428.2 (RK), D429.2 (RK), D430.2 (RK), D431.2 (RK), D432.2 (RK); also elsewhere on the board
/Red27: D433.2 (RK), D434.2 (RK), D435.2 (RK), D436.2 (RK), D437.2 (RK), D438.2 (RK), D439.2 (RK), D440.2 (RK), D441.2 (RK), D442.2 (RK), D443.2 (RK), D444.2 (RK), D445.2 (RK), D446.2 (RK), D447.2 (RK), D448.2 (RK); also elsewhere on the board
/Red28: D449.2 (RK), D450.2 (RK), D451.2 (RK), D452.2 (RK), D453.2 (RK), D454.2 (RK), D455.2 (RK), D456.2 (RK), D457.2 (RK), D458.2 (RK), D459.2 (RK), D460.2 (RK), D461.2 (RK), D462.2 (RK), D463.2 (RK), D464.2 (RK); also elsewhere on the board
/Red29: D465.2 (RK), D466.2 (RK), D467.2 (RK), D468.2 (RK), D469.2 (RK), D470.2 (RK), D471.2 (RK), D472.2 (RK), D473.2 (RK), D474.2 (RK), D475.2 (RK), D476.2 (RK), D477.2 (RK), D478.2 (RK), D479.2 (RK), D480.2 (RK); also elsewhere on the board
/Red30: D481.2 (RK), D482.2 (RK), D483.2 (RK), D484.2 (RK), D485.2 (RK), D486.2 (RK), D487.2 (RK), D488.2 (RK), D489.2 (RK), D490.2 (RK), D491.2 (RK), D492.2 (RK), D493.2 (RK), D494.2 (RK), D495.2 (RK), D496.2 (RK); also elsewhere on the board
/Red31: D497.2 (RK), D498.2 (RK), D499.2 (RK), D500.2 (RK), D501.2 (RK), D502.2 (RK), D503.2 (RK), D504.2 (RK), D505.2 (RK), D506.2 (RK), D507.2 (RK), D508.2 (RK), D509.2 (RK), D510.2 (RK), D511.2 (RK), D512.2 (RK); also elsewhere on the board

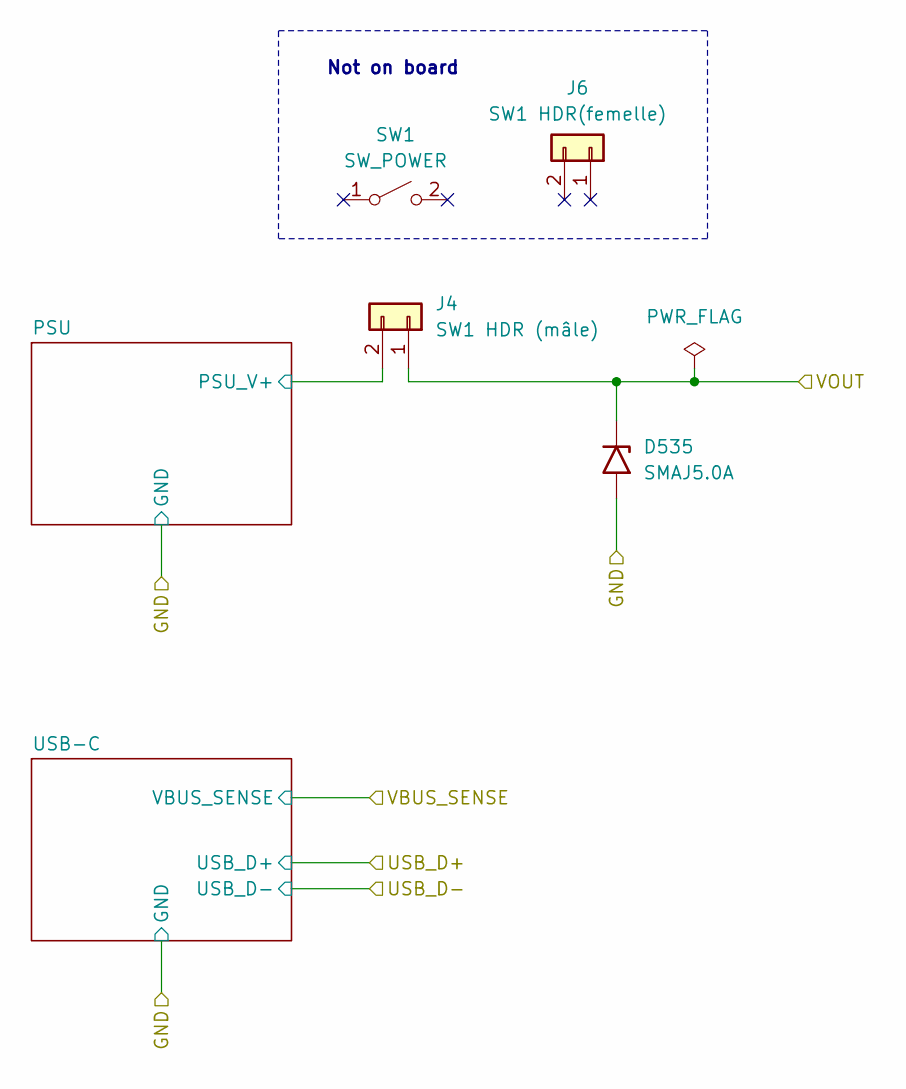
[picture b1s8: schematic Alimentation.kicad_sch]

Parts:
D535: SMAJ5.0A; P6SMAJ5.0; DigiKey PN 31-P6SMAJ5.0ADF-13CT-ND
J4: SW1 HDR (mâle); PinHeader_1x02_P2.54mm_Horizontal; DigiKey PN S9499-ND
J6: SW1 HDR(femelle); DigiKey PN S9435-ND
SW1: SW_POWER; DigiKey PN CKN11875-ND

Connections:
+5V: D535.1 (A1), J4.1; also elsewhere on the board
/Alimentation/PSU/PSU_V+: J4.2; also elsewhere on the board
GND: D535.2 (A2); also elsewhere on the board

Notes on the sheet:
Not on board
